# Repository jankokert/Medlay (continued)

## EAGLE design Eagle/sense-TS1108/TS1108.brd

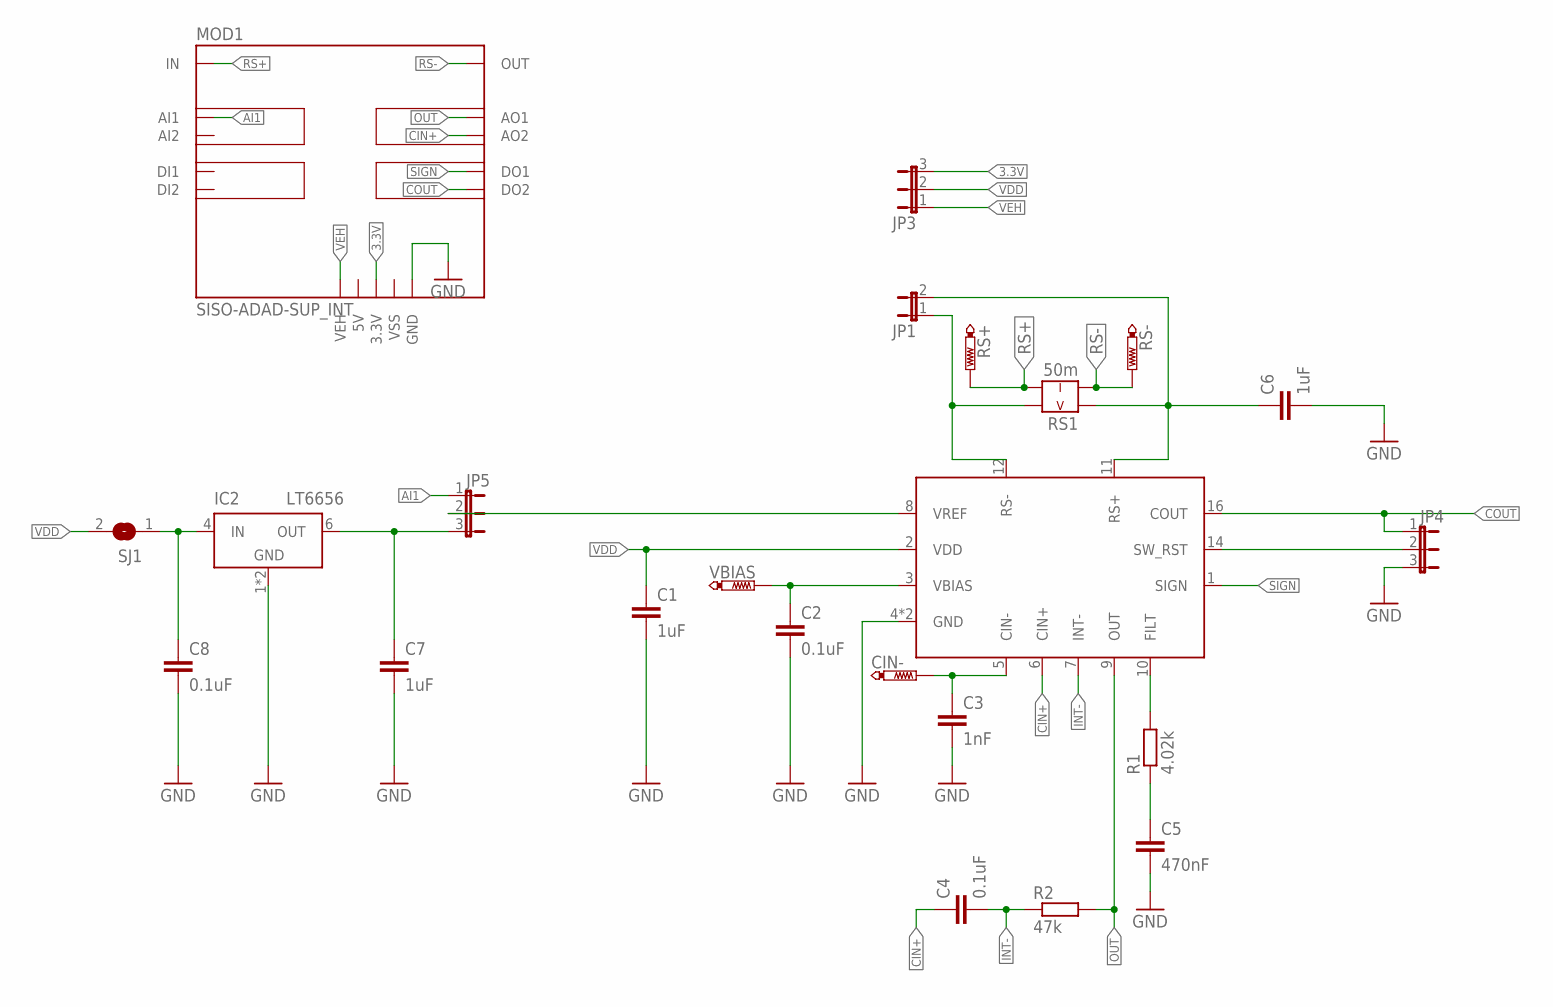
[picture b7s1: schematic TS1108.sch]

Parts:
C1, C6, C7: 1uF; C0805K
C2, C4, C8: 0.1uF; C0805K
C3: 1nF; C0805K
C5: 470nF; C0805K
CIN-: PTR1B1,27; B1,27
IC1: TS1108; LFCSP16_WQ_CP-16-33
IC2: LT6656; TSOT23-6
JP1: JP1E; JP1
JP3, JP4, JP5: JP2E; JP2
MOD1: SISO-ADAD-SUP_INT; SISO-ADAD-SUP
R1: 4.02k; R0805
R2: 47k; R0805
RS1: 50m; LVK12
RS+: PTR1B1,27; B1,27
RS-: PTR1B1,27; B1,27
SJ1: SJ
VBIAS: PTR1B1,27; B1,27

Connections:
3.3V: JP3.3, MOD1.3.3V
5V: MOD1.5V
AI1: JP5.1, MOD1.AI1
CIN+: C4.1, IC1.6 (CIN+), MOD1.AO2
CIN-: C3.1, CIN-.TP, IC1.5 (CIN-)
COUT: IC1.16 (COUT), JP4.1, MOD1.DO2
GND: C1.2, C2.2, C3.2, C5.2, C6.2, C7.2, C8.2, IC1.4 (GND), IC1.EXP (GND), IC2.1 (GND), IC2.2 (GND), JP4.3, MOD1.GND1 (GND), MOD1.GND2 (GND), MOD1.GND3 (GND), MOD1.GND4 (GND)
INT-: C4.2, IC1.7 (INT-), R2.1
unnamed: C2.1, IC1.3 (VBIAS), VBIAS.TP
unnamed: C7.1, IC2.6 (OUT), JP5.3
unnamed: C8.1, IC2.4 (IN), SJ1.1
unnamed: C6.1, IC1.11 (RS+), JP1.2, RS1.V1
unnamed: IC1.8 (VREF), JP5.2
unnamed: IC1.10 (FILT), R1.2
unnamed: C5.1, R1.1
unnamed: IC1.14 (SW_RST), JP4.2
unnamed: IC1.12 (RS-), JP1.1, RS1.V2
OUT: IC1.9 (OUT), MOD1.AO1, R2.2
RS+: MOD1.IN1 (IN), MOD1.IN2 (IN), MOD1.IN3 (IN), MOD1.IN4 (IN), RS1.I2, RS+.TP
RS-: MOD1.OUT1_1 (OUT), MOD1.OUT1_2 (OUT), MOD1.OUT1_3 (OUT), MOD1.OUT1_4 (OUT), RS1.I1, RS-.TP
SIGN: IC1.1 (SIGN), MOD1.DO1
VDD: C1.1, IC1.2 (VDD), JP3.2, SJ1.2
VEH: JP3.1, MOD1.VEH
VSS: MOD1.VSS

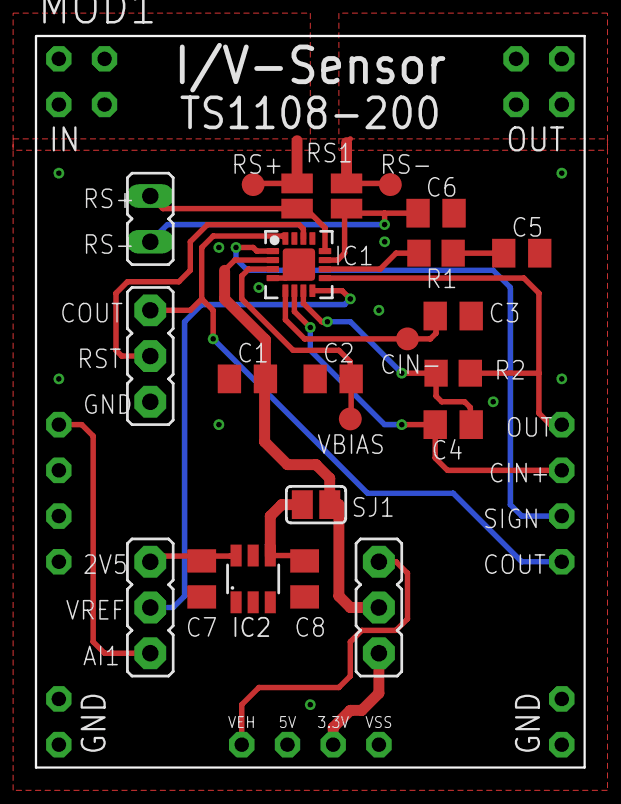
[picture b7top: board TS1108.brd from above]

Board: 2 copper layers, 30.5 x 40.6 mm, 23 parts (0 on the bottom side), 22 nets.

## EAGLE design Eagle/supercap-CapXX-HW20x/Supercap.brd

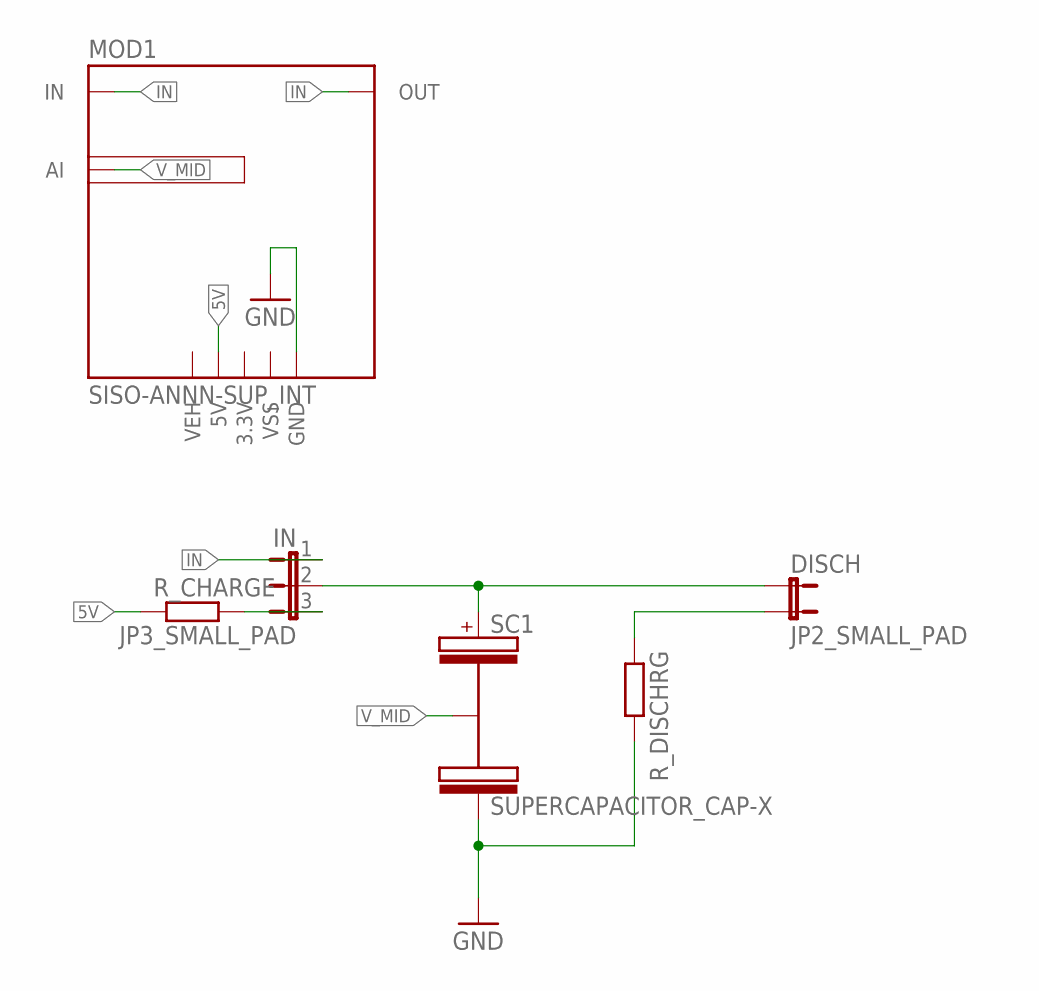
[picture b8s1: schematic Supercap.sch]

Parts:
DISCH: JP2_SMALL_PAD
IN: JP3_SMALL_PAD
MOD1: SISO-ANNN-SUP_INT; SISO-ANNN-SUP
R_CHARGE: R_THROUGH-HOLE
R_DISCHRG: R_THROUGH-HOLE
SC1: SUPERCAPACITOR_CAP-X

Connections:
3.3V: MOD1.3.3V
5V: MOD1.5V, R_CHARGE.1
GND: MOD1.GND1 (GND), MOD1.GND2 (GND), MOD1.GND3 (GND), MOD1.GND4 (GND), R_DISCHRG.2, SC1.-1
IN: IN.1, MOD1.IN1 (IN), MOD1.IN2 (IN), MOD1.IN3 (IN), MOD1.IN4 (IN), MOD1.OUT1 (OUT), MOD1.OUT2 (OUT), MOD1.OUT3 (OUT), MOD1.OUT4 (OUT)
unnamed: IN.3, R_CHARGE.2
unnamed: DISCH.1, IN.2, SC1.+
unnamed: DISCH.2, R_DISCHRG.1
VEH: MOD1.VEH
VSS: MOD1.VSS
V_MID: MOD1.AI, SC1.V_MID

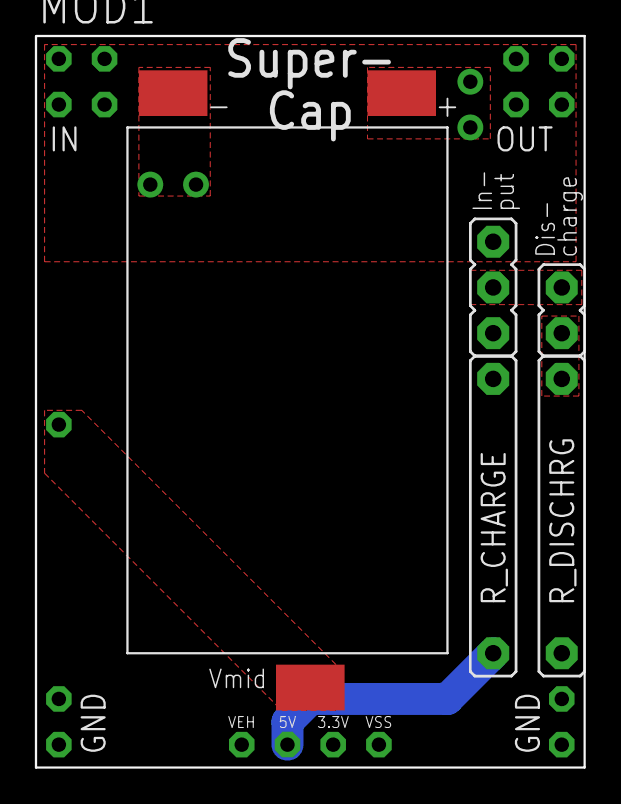
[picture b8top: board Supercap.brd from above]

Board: 2 copper layers, 30.5 x 40.6 mm, 6 parts (0 on the bottom side), 7 nets.
